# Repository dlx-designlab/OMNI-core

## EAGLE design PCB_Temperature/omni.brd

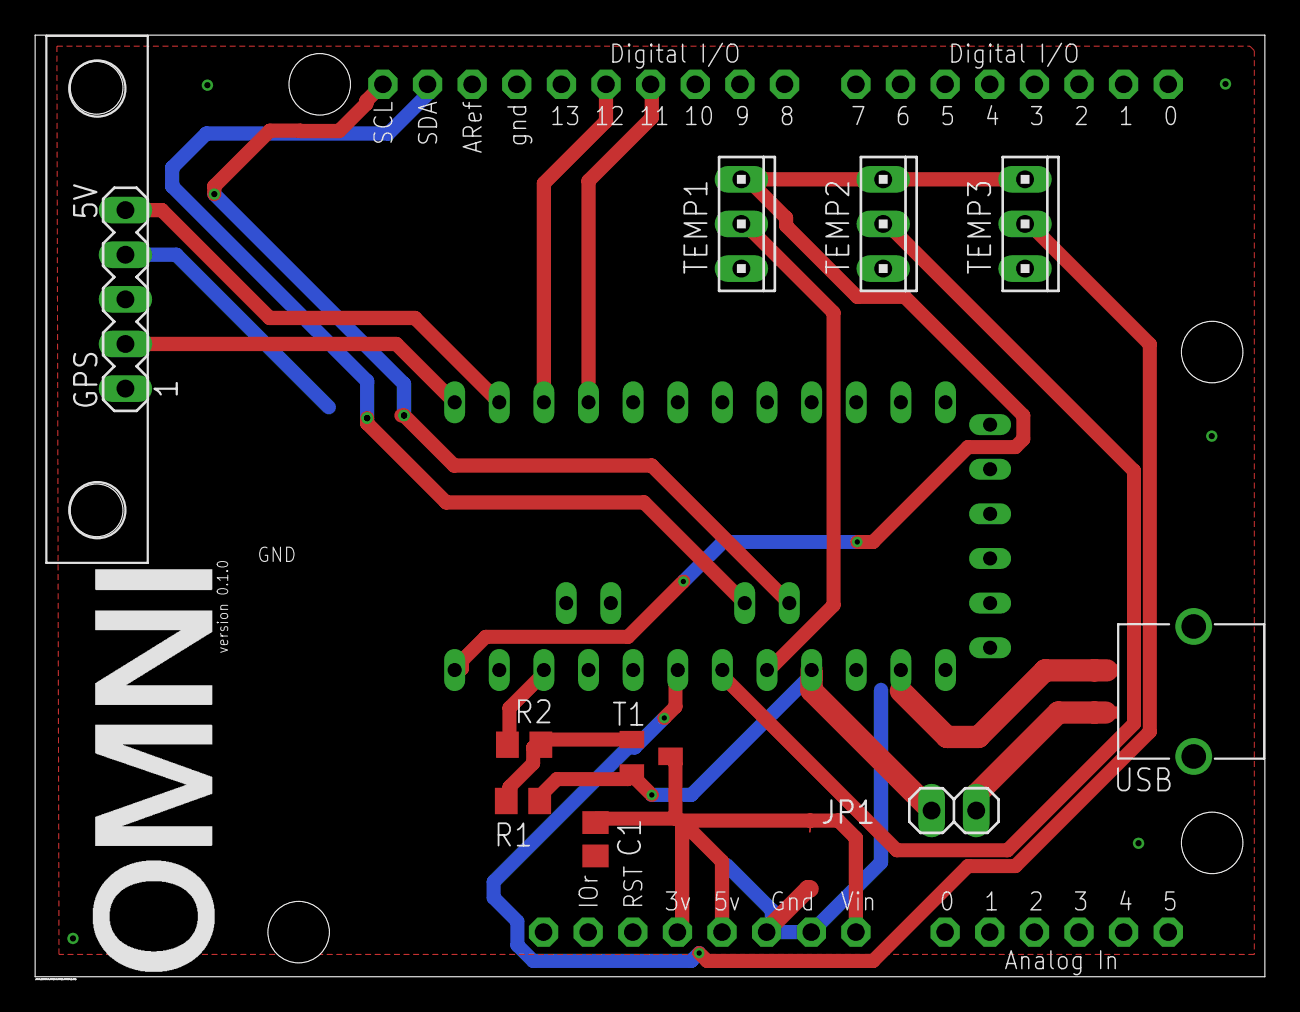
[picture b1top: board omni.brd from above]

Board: 2 copper layers, 70.0 x 53.6 mm, 12 parts (0 on the bottom side), 16 nets.

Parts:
C1: C0805
GPS: AE-GYSFDMAXB; MA05-1
JP1: 1X02
LTE_LORA: ARDUINOR3-BPLACE
R1, R2: R0805
T1: SOT23
TEMP1, TEMP2, TEMP3: 10X03MTA
U$1: PRO-MINI-2
USB: MICROUSBCON

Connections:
GND: C1.2, GPS.4, LTE_LORA.GND, LTE_LORA.GND1, LTE_LORA.GND2, TEMP1.1, TEMP2.1, TEMP3.1, U$1.GND, USB.GND
unnamed: GPS.2, U$1.D9
unnamed: GPS.5, U$1.D8
unnamed: TEMP1.2, U$1.A0
unnamed: C1.1, LTE_LORA.3V, LTE_LORA.5V, LTE_LORA.VIN, T1.3
unnamed: TEMP2.2, U$1.A1
unnamed: TEMP1.3, TEMP2.3, TEMP3.3, U$1.D10
unnamed: JP1.2, USB.5V
unnamed: LTE_LORA.SDA, U$1.A4
unnamed: LTE_LORA.SCL, U$1.A5
unnamed: LTE_LORA.D12, U$1.D7
unnamed: LTE_LORA.D11, U$1.D6
S$1: R1.2, R2.2, T1.1
S$3: R2.1, U$1.D12
S$4: TEMP3.2, U$1.A2
V+: JP1.1, R1.1, T1.2, U$1.VCC

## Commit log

2020-12-10 Lake Hamanako version
2020-12-10 Lake Hamanako salinity calibration
2020-12-10 Version 3
2020-12-10 Version4
2020-12-10 Zushi beach working version
    Surface temp., 1m depth temp., 2m depth temp.
2020-12-10 tmp tests
2020-12-16 Add new code for Analog temp ss
2020-12-19 Add PCB Eagle project for Temperature
2020-12-23 Revise powersource for LoRa
2020-12-25 Update MKIII_v5.1
    Remove Salinity sensor implementation
    Remove LoRa Power source control
2021-01-12 Add LTE + TMP36
    OMNI_MKIII_v5.2 for TMP36 + LTE
2021-01-15 Update NetworkPower ON-OFF code
2021-01-18 Pre-define temperature pin mode to make sure
2021-01-29 Modify TMP35 board with power saving
2021-03-15 Fix the missing connection with Temp3
